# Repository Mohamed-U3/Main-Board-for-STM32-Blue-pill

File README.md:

# Main Board for STM32 Blue Pill

A custom PCB main board designed to extend JST cables for STM32F103C8T6 Blue Pill microcontroller board. This board provides organized connections for displays, sensors, buttons, and communication modules with proper ESD protection.

## 📋 Overview

This project is a breakout/expansion board for the STM32 Blue Pill that simplifies connections to various peripherals through organized connectors. The board features dedicated interfaces for TFT displays, laser range finders, sensors, and a 10-button.

### Key Features

- **Compact Design**: 60mm × 40mm PCB size
- **ESD Protection**: Built-in protection diodes for all I/O pins
- **Multiple Interfaces**: SPI, UART communication support
- **Organized Connectors**: Dedicated connectors for different peripheral types
- **Buttons**: Support for 10 buttons with internal pull-up configuration
- **Programming Interface**: SWD debugging/programming connector

## 🔌 Connectors & Pin Assignments

### J1 - TFT Display Connector (8 pins)

Standard SPI TFT display interface with power and control signals.

```
Pin | Signal | STM32 Pin | Description
----|--------|-----------|-------------
1   | CS     | PA4       | SPI Chip Select
2   | BLK    | PA3       | Backlight control (PWM)
3   | DC     | PA1       | Data/Command select
4   | RES    | PA2       | Reset signal
5   | MOSI   | PA7       | SPI Data Out (SPI1_MOSI)
6   | CLK    | PA5       | SPI Clock (SPI1_SCK)
7   | VCC    | 3.3V      | Power supply
8   | GND    | GND       | Ground
```

### J2 - LRF (Laser Range Finder) Connector (6 pins)

UART interface for laser distance measurement modules.

```
Pin | Signal | STM32 Pin | Description
----|--------|-----------|-------------
1   | VCC    | VIN       | Power supply (5V tolerant)
2   | GND    | GND       | Ground
3   | Rx     | PA10      | UART Receive (USART1_RX)
4   | Tx     | PA9       | UART Transmit (USART1_TX)
5   | En     | 3.3V      | Enable signal
6   | GND    | GND       | Additional ground connection
```

### J3 - Button Connector 1 (6 pins)

First set of button inputs with internal pull-up resistors.

```
Pin | Signal | STM32 Pin | Description
----|--------|-----------|-------------
1   | GND    | GND       | Common ground
2   | BTN1   | PB4       | Button 1 input
3   | BTN2   | PA15      | Button 2 input
4   | BTN3   | PA12      | Button 3 input
5   | BTN4   | PA8       | Button 4 input
5   | BTN5   | PB15      | Button 5 input
```

### J4 - Button Connector 2 (6 pins)

Second set of button inputs with internal pull-up resistors.

```
Pin | Signal | STM32 Pin | Description
----|--------|-----------|-------------
1   | GND    | GND       | Common ground
2   | BTN6   | PB5       | Button 6 input
3   | BTN7   | PB6       | Button 7 input
4   | BTN8   | PB7       | Button 8 input
5   | BTN9   | PB8       | Button 9 input
5   | BTN10  | PB9       | Button 10 input
```

### J5 - Sensor Connector (5 pins)

SPI interface for various sensors (IMU, compass, temperature, etc.).

```
Pin | Signal | STM32 Pin | Description
----|--------|-----------|-------------
1   | VCC    | 3.3V      | Power supply
2   | CS     | PB12      | Chip Select (SPI2_NSS)
3   | CLK    | PB13      | SPI Clock (SPI2_SCK)
4   | MISO   | PB14      | SPI Data In (SPI2_MISO)
5   | GND    | GND       | Ground
```

### J6 - SWD Connector (4 pins)

SWD interface for Programming & debbugging.

```
Pin | Signal | STM32 Pin | Description
----|--------|-----------|-------------
1   | VCC    | 3.3V      | Power supply
2   | SWDIO  | SWDIO     | Serial Wire Debug Input Output data
3   | SWDCLK | SWDCLK    | Serial Wire Debug Clock
4   | GND    | GND       | Ground
```

### J7 - Power Connector (2 pins)

Power input for the system

```
Pin | Signal | STM32 Pin | Description
----|--------|-----------|-------------
1   | VCC    | 5V        | System Power supply
2   | GND    | GND       | Ground
```

### J8 - Brightness SW Connector (4 pins)

Switch to select the Brightness of the TFT

```
Pin | Signal | STM32 Pin | Description
----|--------|-----------|-------------
1   | Level1 | PB0       | Brightness Level 1
2   | Level2 | PB1       | Brightness Level 2
3   | Level3 | PB10      | Brightness Level 3
4   | Level4 | PB11      | Brightness Level 4
```

### U1 - STM32 Blue Pill Socket

Standard 40-pin socket for STM32F103C8T6 Blue Pill board with organized breakout connections.

## 🔒 ESD Protection

The board includes comprehensive ESD protection for all I/O connections:

- **LESD8D3.3N3T5G** diodes for 3.3V signal protection
- **CESD5V0D3** diodes for 5V tolerant pins
- Protection on all connector pins to prevent damage from static discharge

## 🎯 Button Configuration

All 10 buttons are configured for **internal pull-up** operation:

| Button | STM32 Pin | GPIO Mode       | Notes                        |
| ------ | --------- | --------------- | ---------------------------- |
| 1      | PA8       | Input + Pull-up | TIM1_CH1 alternate function  |
| 2      | PA12      | Input + Pull-up | USB_DP alternate function    |
| 3      | PA15      | Input + Pull-up | SPI3_NSS alternate function  |
| 4      | PB4       | Input + Pull-up | SPI3_MISO alternate function |
| 5      | PB5       | Input + Pull-up | SPI3_MOSI alternate function |
| 6      | PB6       | Input + Pull-up | I2C1_SCL, TIM4_CH1 alternate |
| 7      | PB7       | Input + Pull-up | I2C1_SDA, TIM4_CH2 alternate |
| 8      | PB8       | Input + Pull-up | TIM4_CH3 alternate function  |
| 9      | PB9       | Input + Pull-up | TIM4_CH4 alternate function  |
| 10     | PB15      | Input + Pull-up | SPI2_MOSI alternate function |

## 📐 PCB Specifications

- **Dimensions**: 60mm × 40mm
- **Layers**: 2-layer PCB design
- **Design Tool**: KiCad EDA v9.0.3
- **Mounting**: Multiple mounting holes for secure installation
- **Copper Weight**: Standard 1oz copper thickness
- **Via Size**: Standard 0.4mm drill, 0.7mm pad
- **Minimum Track Width**: 0.4mm

## 📁 Repository Contents

```
├── D98.kicad_pcb              	# PCB layout file
├── D98.kicad_sch              	# Schematic file  
├── D98.kicad_pro              	# KiCad project file
├── bom/                       	# Bill of Materials
│   └── bom.csv               	# Component list with part numbers
├── production/                	# Manufacturing files
│   ├── gerbers/              	# Gerber files for PCB fab
│   ├── drill/                	# NC drill files
│   └── pick_and_place/       	# Assembly files
├── 3D output/                 	# 3D renderings (Step files)
└── fabrication-toolkit-options.json
```

## 🚀 Getting Started

### Prerequisites

- STM32F103C8T6 Blue Pill development board
- KiCad EDA software (for viewing/editing design files)
- ST-Link V2 programmer or compatible SWD interface
- Peripheral modules (TFT display, sensors, laser range finder)

### Hardware Assembly

1. **Install Blue Pill**: Solder the Blue Pill board into the U1 socket
2. **ESD Protection**: Install all ESD protection diodes (refer to schematic)
3. **Connectors**: Solder pin headers or JST connectors for J1-J6
4. **Programming Interface**: Install SWD connector (U2)
5. **Testing**: Verify all connections with multimeter before power-on

### Software Setup

1. Install STM32CubeIDE or PlatformIO with STM32 support
2. Configure GPIO pins according to the pin assignment table
3. Enable internal pull-ups for button pins in your initialization code
4. Set up SPI1 for TFT display communication
5. Configure SPI2 for sensor communication
6. Set up USART1 for laser range finder communication

## 🔧 Usage Examples

### TFT Display Connection

```c
// SPI1 configuration for TFT
// PA5 - SPI1_SCK (Clock)
// PA7 - SPI1_MOSI (Data)
// PA4 - CS (Chip Select)
// PA1 - DC (Data/Command)
// PA2 - RES (Reset)
// PA3 - Backlight control (PWM)
```

### Sensor Interface

```c
// SPI2 configuration for sensors
// PB13 - SPI2_SCK (Clock)
// PB14 - SPI2_MISO (Data In)
// PB12 - SPI2_NSS/CS (Chip Select)
```

### UART Communication

```c
// USART1 configuration for LRF
// PA9  - USART1_TX (Transmit)
// PA10 - USART1_RX (Receive)
// Baud rate: 9600-115200 (module dependent)
```

### Button Reading

```c
// Configure buttons with internal pull-up
// Active LOW logic (pressed = 0, released = 1)
// Debouncing recommended in software
```

## ⚡ Power Requirements

- **Input Voltage**: 5V via USB or external supply
- **Logic Level**: 3.3V (regulated by Blue Pill)
- **Current Consumption**:
  - MCU: ~10mA
  - TFT Display: 20-100mA
  - Sensors: 1-10mA each
  - LRF Module: 50-700mA

## 🛠️ Troubleshooting

### Common Issues

1. **No Display Output**: Check SPI connections and power supply
2. **Button Not Responding**: Verify internal pull-up configuration
3. **Sensor Communication Failure**: Check SPI2 pin assignments
4. **Programming Issues**: Ensure SWD connections are correct

### Debug Tips

- Use multimeter to verify 3.3V power rail
- Check continuity of all connector pins
- Verify Blue Pill is properly seated in socket
- Monitor current consumption to detect short circuits

## 📄 License

This project is licensed under the MIT License - see the [LICENSE](LICENSE) file for details.

## 👤 Author

**Mohamed Yousry Ragab**

- **GitHub**: [@Mohamed-U3](https://github.com/Mohamed-U3)
- **LinkedIn**: [mohamed-u3](https://www.linkedin.com/in/mohamed-u3/)
- **Email**: Contact via GitHub profile
- **Specialization**: Embedded Systems & PCB Design

## 🤝 Contributing

Contributions are welcome! Please feel free to submit:

- Bug reports and feature requests via [Issues](https://github.com/Mohamed-U3/Main-Board-for-STM32-Blue-pill/issues)
- Code improvements via Pull Requests
- Documentation enhancements
- Hardware testing feedback

### Development Guidelines

1. Follow KiCad design rules and conventions
2. Test all changes on actual hardware
3. Update documentation for any pin assignment changes
4. Maintain backward compatibility when possible

## 🔗 Related Projects

- [StopWatch_STM32F103](https://github.com/Mohamed-U3/StopWatch_STM32F103) - Stopwatch project using STM32F103
- *More STM32 projects coming soon...*

## 📊 Version History

- **v1.0** - Initial release with basic functionality
- **v1.1** - Added ESD protection and improved routing
- **v1.2** - Updated connector layout and pin assignments
- **v2.0** - Updated connector layout, pin assignments, and silkscreen.
- **v3.0** - Change the EN pin of the TFT from Vcc for full brightness always to be controlled via GPIO A6.
- **v3.1** - Change the EN pin of the TFT to A3 because A6 is MISO pin.
- **v3.2** - Change the Rounting of Tracks and the silkscreen.

## 📞 Support

For technical support:

1. Check the [Issues](https://github.com/Mohamed-U3/Main-Board-for-STM32-Blue-pill/issues) page
2. Review the troubleshooting section above
3. Create a new issue with detailed description and photos if needed

---

*This README reflects the D98 PCB design with corrected pin assignments. Always verify connections against the actual schematic before assembly.*

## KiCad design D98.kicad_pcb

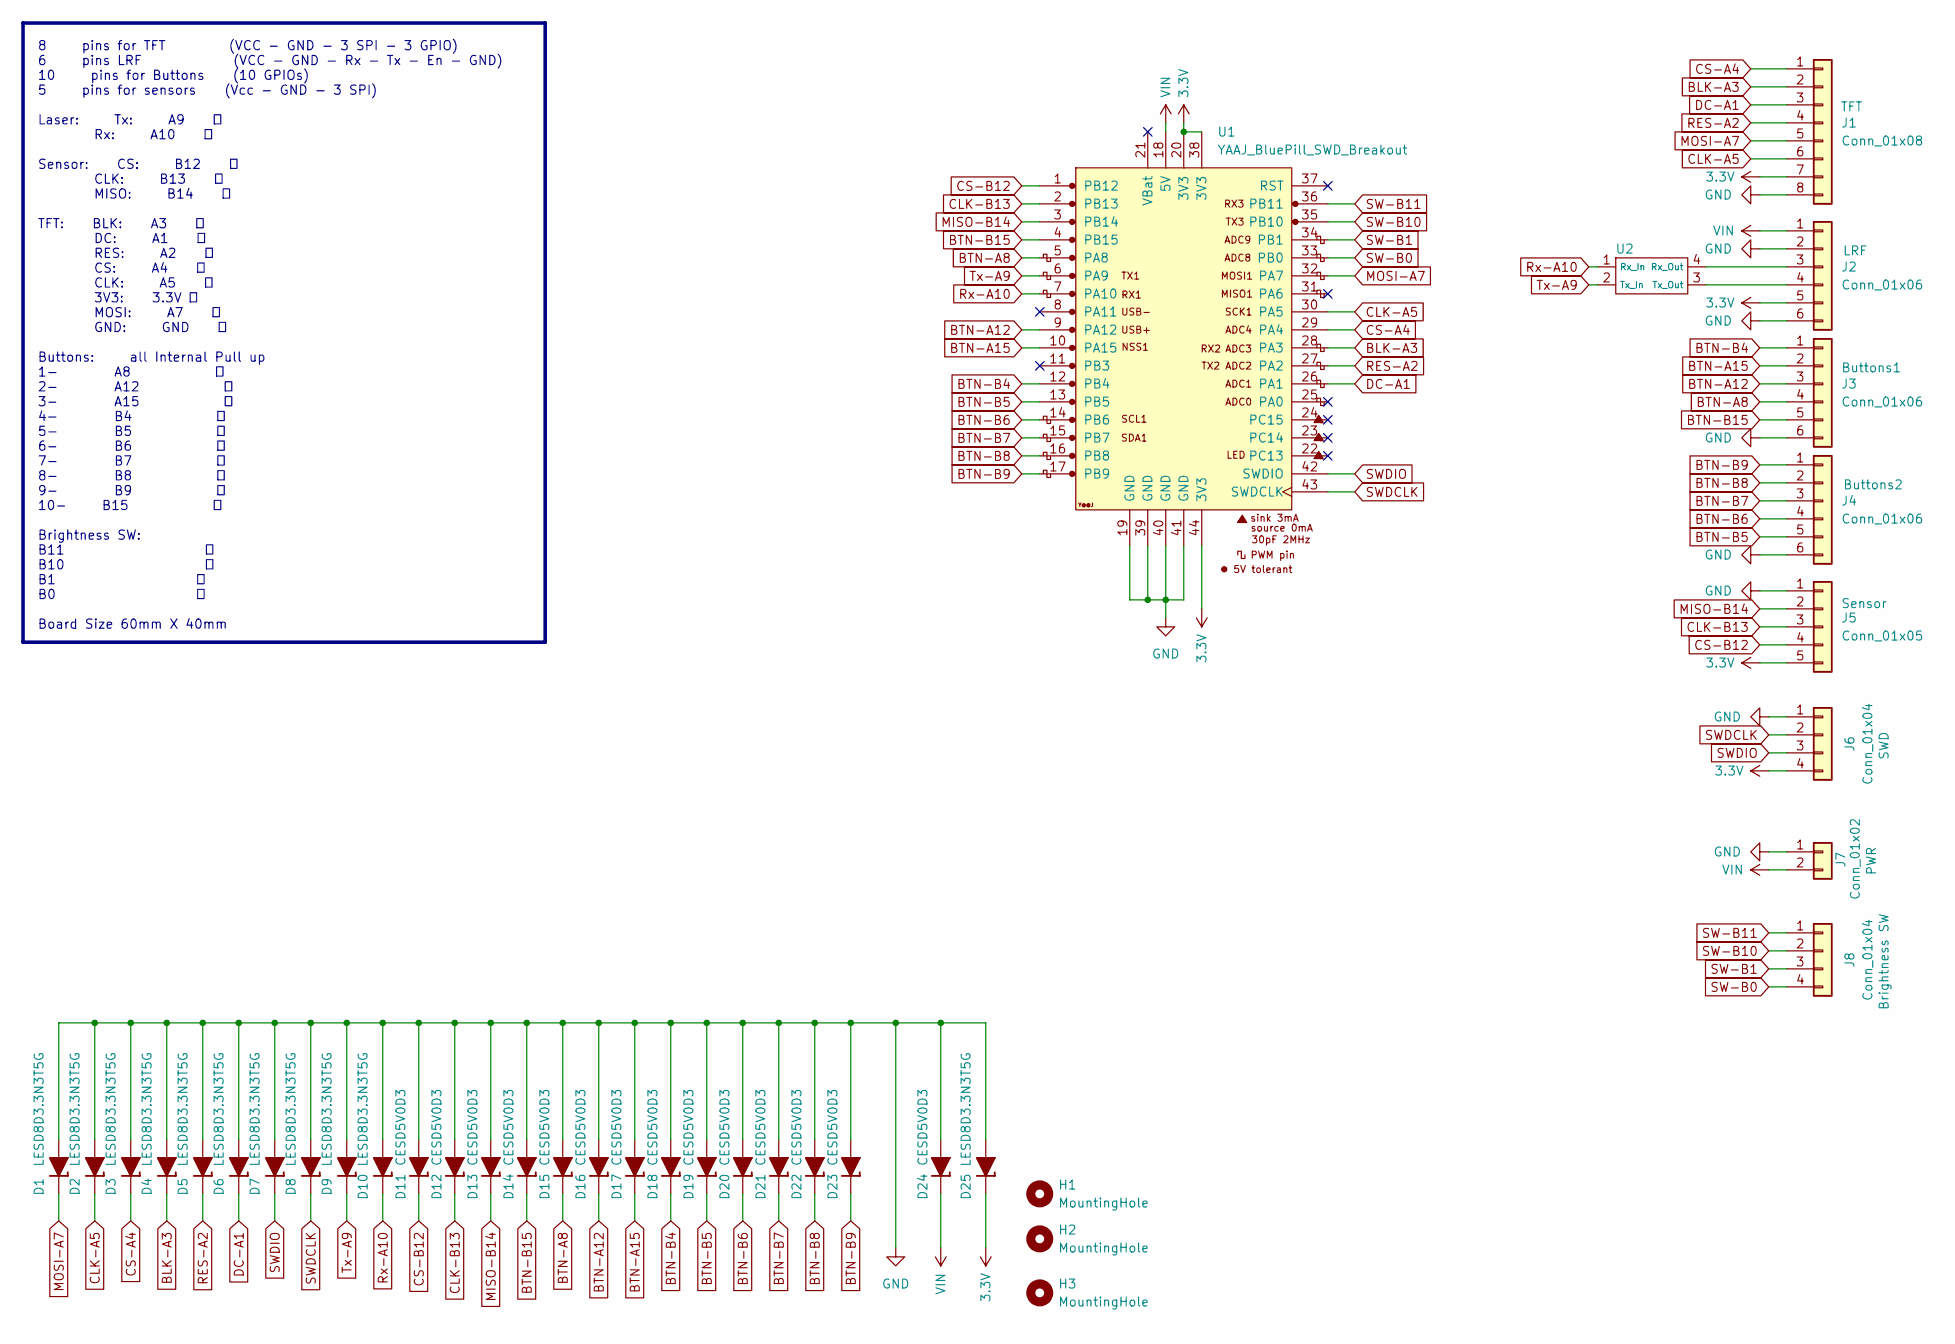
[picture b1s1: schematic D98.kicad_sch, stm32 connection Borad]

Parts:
D1, D2, D3, D4, D5, D6, D7, D8, D9, D10, D25: LESD8D3.3N3T5G; D_SOD-882D
D11, D12, D13, D14, D15, D16, D17, D18, D19, D20, D21, D22, D23, D24: CESD5V0D3; D_SOD-323_HandSoldering
H1, H2, H3: MountingHole; MountingHole_2.5mm
J1: Conn_01x08; JST_XH_B8B-XH-A_1x08_P2.50mm_Vertical
J2, J3, J4: Conn_01x06; JST_XH_B6B-XH-A_1x06_P2.50mm_Vertical
J5: Conn_01x05; JST_XH_B5B-XH-A_1x05_P2.50mm_Vertical
J6: Conn_01x04; JST_XH_B4B-XH-A_1x04_P2.50mm_Vertical
J7: Conn_01x02; JST_XH_B2B-XH-A_1x02_P2.50mm_Vertical
J8: Conn_01x04; JST_XH_S4B-XH-A-1_1x04_P2.50mm_Horizontal
U1: YAAJ_BluePill_SWD_Breakout; YAAJ BluePill_SWD_2
U2: Poka Yoke; poka-yoke_rxtx

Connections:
3.3V: D25.1 (K), J1.7, J2.5, J5.5, J6.4, U1.20 (3V3), U1.38 (3V3), U1.44 (3V3)
BLK-A3: D4.1 (K), J1.2, U1.28 (PA3)
BTN-A8: D15.1 (K), J3.4, U1.5 (PA8)
BTN-A12: D16.1 (K), J3.3, U1.9 (PA12)
BTN-A15: D17.1 (K), J3.2, U1.10 (PA15)
BTN-B4: D18.1 (K), J3.1, U1.12 (PB4)
BTN-B5: D19.1 (K), J4.5, U1.13 (PB5)
BTN-B6: D20.1 (K), J4.4, U1.14 (PB6)
BTN-B7: D21.1 (K), J4.3, U1.15 (PB7)
BTN-B8: D22.1 (K), J4.2, U1.16 (PB8)
BTN-B9: D23.1 (K), J4.1, U1.17 (PB9)
BTN-B15: D14.1 (K), J3.5, U1.4 (PB15)
CLK-A5: D2.1 (K), J1.6, U1.30 (PA5)
CLK-B13: D12.1 (K), J5.3, U1.2 (PB13)
CS-A4: D3.1 (K), J1.1, U1.29 (PA4)
CS-B12: D11.1 (K), J5.4, U1.1 (PB12)
DC-A1: D6.1 (K), J1.3, U1.26 (PA1)
GND: D1.2 (A), D2.2 (A), D3.2 (A), D4.2 (A), D5.2 (A), D6.2 (A), D7.2 (A), D8.2 (A), D9.2 (A), D10.2 (A), D11.2 (A), D12.2 (A), D13.2 (A), D14.2 (A), D15.2 (A), D16.2 (A), D17.2 (A), D18.2 (A), D19.2 (A), D20.2 (A), D21.2 (A), D22.2 (A), D23.2 (A), D24.2 (A), D25.2 (A), J1.8, J2.2, J2.6, J3.6, J4.6, J5.1, J6.1, J7.1, U1.19 (GND), U1.39 (GND), U1.40 (GND), U1.41 (GND)
MISO-B14: D13.1 (K), J5.2, U1.3 (PB14)
MOSI-A7: D1.1 (K), J1.5, U1.32 (PA7)
unnamed: J2.3, U2.4 (Rx_Out)
unnamed: J2.4, U2.3 (Tx_Out)
RES-A2: D5.1 (K), J1.4, U1.27 (PA2)
Rx-A10: D10.1 (K), U1.7 (PA10), U2.1 (Rx_In)
SW-B0: J8.4, U1.33 (PB0)
SW-B1: J8.3, U1.34 (PB1)
SW-B10: J8.2, U1.35 (PB10)
SW-B11: J8.1, U1.36 (PB11)
SWDCLK: D8.1 (K), J6.2, U1.43 (SWDCLK)
SWDIO: D7.1 (K), J6.3, U1.42 (SWDIO)
Tx-A9: D9.1 (K), U1.6 (PA9), U2.2 (Tx_In)
VIN: D24.1 (K), J2.1, J7.2, U1.18 (5V)

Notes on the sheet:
8 pins for TFT (VCC - GND - 3 SPI - 3 GPIO) 6 pins LRF (VCC - GND - Rx - Tx - En - GND) 10 pins for Buttons (10 GPIOs) 5 pins for sensors (Vcc - GND - 3 SPI) Laser: Tx: A9 ✅ Rx: A10 ✅ Sensor: CS: B12 ✅ CLK: B13 ✅ MISO: B14 ✅ TFT: BLK: A3 ✅ DC: A1 ✅ RES: A2 ✅ CS: A4 ✅ CLK: A5 ✅ 3V3: 3.3V ✅ MOSI: A7 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

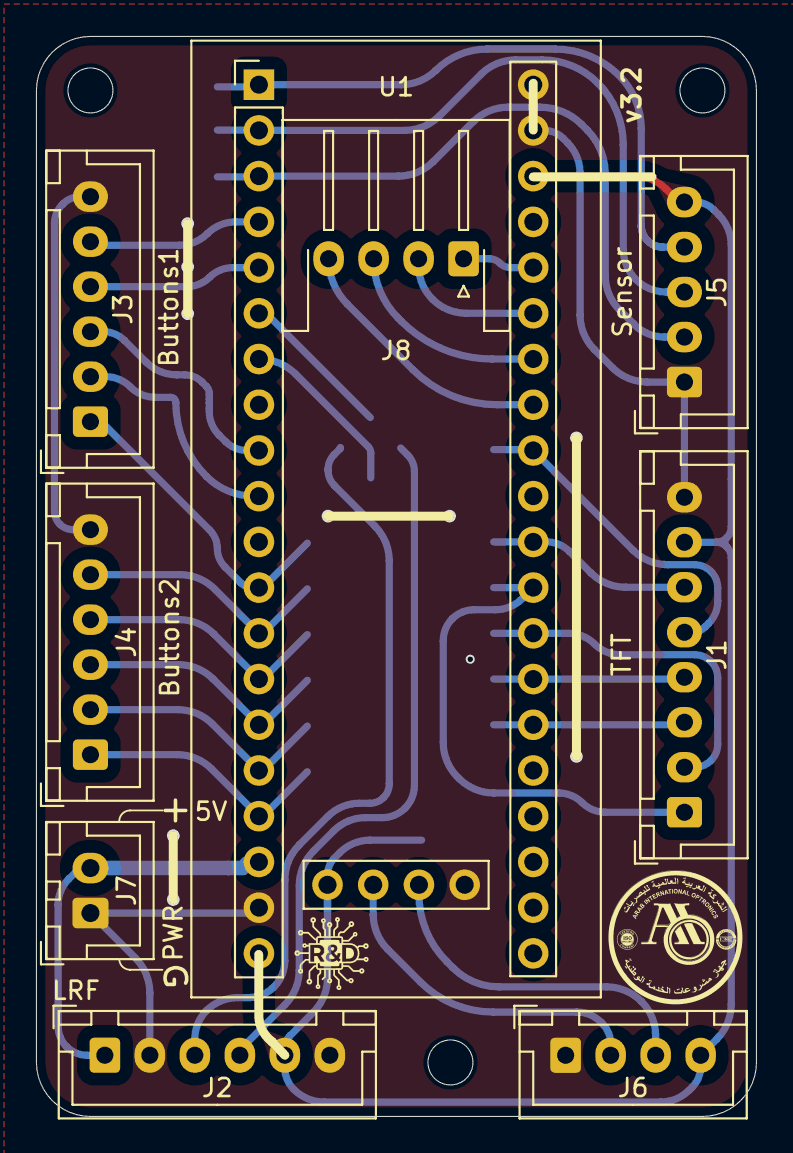
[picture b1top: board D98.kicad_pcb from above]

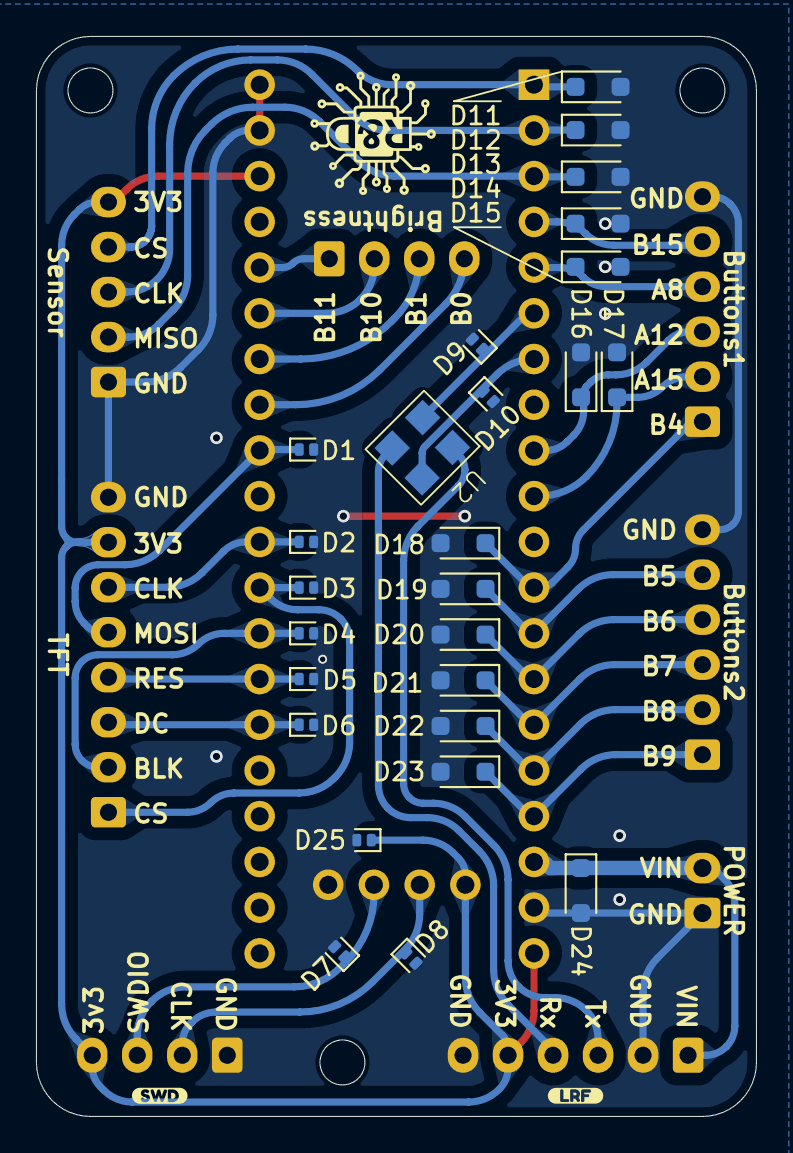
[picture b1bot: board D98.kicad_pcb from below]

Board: 2 copper layers, 40.0 x 60.0 mm, 40 parts (28 on the bottom side), 32 nets.

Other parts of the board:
kibuzzard-699AD153: G***; kibuzzard-699AD153
kibuzzard-699AD186: G***; kibuzzard-699AD186

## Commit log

2025-10-21 first commit: the Board has been created and I'm waiting for some edits tomorrow 😢.
2025-10-22 feat: changed position of MountingHoles Small modefication and Rounding Tracks.
2025-10-22 feat: generating Fabriccations Files.
2025-10-29 Fix: -SWD pins wasn't installed correctlly now the connection is correct. -adding some pin assignment in the back side.
2025-10-30 Feat & Edit: changer the position of the TVSes & adding Connector.
2025-11-04 Fix: adding teardrop for the GPIO of the last added connector.
2025-11-05 Fix: Changing the EN pin of TFT from always full Brightness to becontrolled Via PWM Pin.
2025-11-05 doc: adding images and edit README.md file.
2025-11-05 fix: Images in README.md file is now appears.
2025-11-05 fix: changed the EN pin GPIO agian from A6 to A3 because A6 is MSIO.
2026-02-22 Feat: Change the Rounting of Tracks and the silkscreen.
